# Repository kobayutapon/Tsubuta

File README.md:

# Tsubuta
Tsubuta is IoT device produced by GDG Shinshu

## Presentation
* [Presentation Document](./Document/Tsubuta_Presentation.pdf.pdf)

## Hardware Information  
* [Hardware Specification](./Hardware/BoardSpec.md)
* [Board schematic](./Hardware/Tsubuta_Schematic.pdf)
* [Firmware](./Hardware/Arduino/Tsubuta_AddOnBoard/Tsubuta_AddOnBoard.ino)

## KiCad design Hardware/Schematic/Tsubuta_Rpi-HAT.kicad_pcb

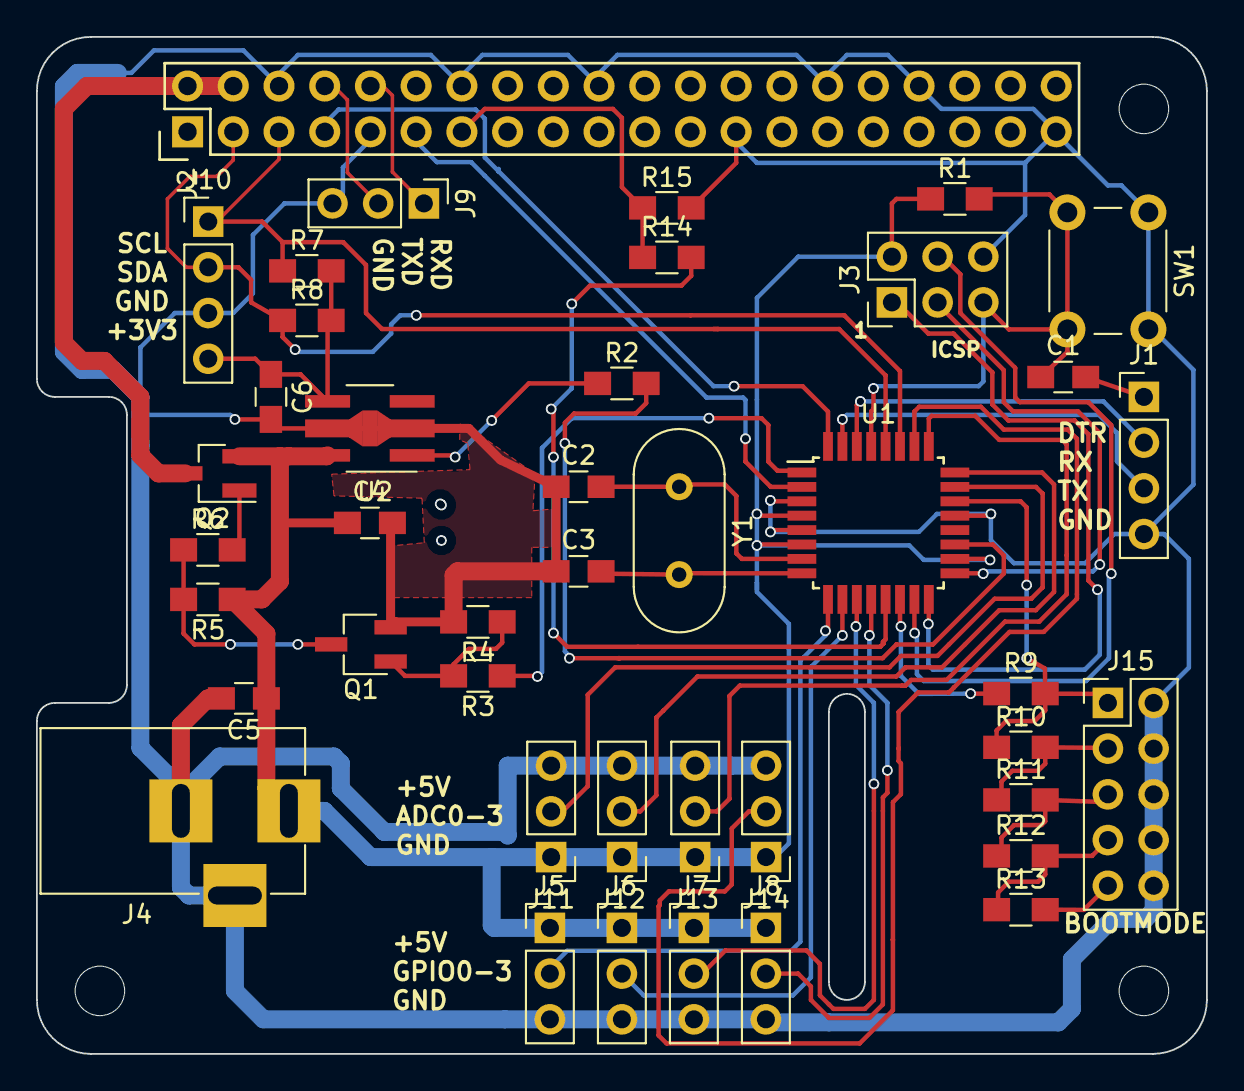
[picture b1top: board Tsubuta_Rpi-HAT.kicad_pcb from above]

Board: 2 copper layers, 65.0 x 56.5 mm, 42 parts (0 on the bottom side), 41 nets.

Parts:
C1: 0.1uF; C_0805_HandSoldering
C2, C3: 22pF; C_0805_HandSoldering
C4: 0.33uF; C_0805_HandSoldering
C5: 22uF; C_0805_HandSoldering
C6: 2.2uF; C_0805_HandSoldering
J1: Conn_01x04; Pin_Header_Straight_1x04_Pitch2.54mm
J2: RPi_GPIO; Pin_Header_Straight_2x20
J3: CN_ICSP; Pin_Header_Straight_2x03_Pitch2.54mm
J4: Jack-DC; BARREL_JACK
J5: GPIO0; Pin_Header_Straight_1x03_Pitch2.54mm
J6: GPIO1; Pin_Header_Straight_1x03_Pitch2.54mm
J7: GPIO2; Pin_Header_Straight_1x03_Pitch2.54mm
J8: GPIO3; Pin_Header_Straight_1x03_Pitch2.54mm
J9: Conn_01x03; Pin_Header_Straight_1x03_Pitch2.54mm
J10: CN_I2C; Pin_Header_Straight_1x04_Pitch2.54mm
J11: ADC0; Pin_Header_Straight_1x03_Pitch2.54mm
J12: ADC1; Pin_Header_Straight_1x03_Pitch2.54mm
J13: ADC2; Pin_Header_Straight_1x03_Pitch2.54mm
J14: ADC3; Pin_Header_Straight_1x03_Pitch2.54mm
J15: BOOTMODE; Pin_Header_Straight_2x05_Pitch2.54mm
Q1: 2SC3325-Y; SC-59_Handsoldering
Q2: IRLML6402(SOT-23); SOT-23_Handsoldering
R1, R2, R3, R4, R5, R6, R7, R8, R9, R11, R12, R13: 10K; R_0805_HandSoldering
R10: 1K; R_0805_HandSoldering
R14: 1.8K; R_0805_HandSoldering
R15: 3.3K; R_0805_HandSoldering
SW1: SW_RST; SW_PUSH_6mm
U1: ATMEGA328P-AU; TQFP-32_7x7mm_Pitch0.8mm
U2: NJM2884U1; SOT-89-5_Housing_Handsoldering
Y1: 16MHz; Crystal_HC49-U_Vertical

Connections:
3V3_ENB: R2.2, U1.19
#ARD_SS: R9.1, U1.14
#RST: C1.1, J3.5, R1.2, SW1.2, U1.29
+3V3: C6.1, J10.4, R7.2, R8.2, U2.4
+5V: C4.1, C5.1, J3.2, J4.1, J5.1, J6.1, J7.1, J8.1, J11.1, J12.1, J13.1, J14.1, Q2.2, R1.1, R5.1, U1.4, U1.6, U1.18, U2.5
ADC0: J11.2, U1.23
ADC1: J12.2, U1.24
ADC2: J13.2, U1.25
ADC3: J14.2, U1.26
ARD_INT_3V3: J2.13, R14.1, R15.1
ARD_INT_5V: R14.2, U1.13
ARD_MISO: J3.1, U1.16
ARD_MOSI: J3.4, U1.15
ARD_RX: J1.2, U1.30
ARD_SCK: J3.3, U1.17
ARD_SCL: J2.5, J10.1, R7.1, U1.28
ARD_SDA: J2.3, J10.2, R8.1, U1.27
ARD_TX: J1.3, U1.31
ARD_XTAL1: C2.2, U1.7, Y1.1
ARD_XTAL2: C3.2, U1.8, Y1.2
BOOTMODE: J15.1, R9.2, R10.1, U1.22
GND: C2.1, C3.1, C4.2, C5.2, C6.2, J1.4, J2.6, J2.9, J2.14, J2.20, J2.25, J2.30, J2.34, J2.39, J3.6, J4.2, J4.3, J5.3, J6.3, J7.3, J8.3, J9.3, J10.3, J11.3, J12.3, J13.3, J14.3, J15.2, J15.4, J15.6, J15.8, J15.10, Q1.2, R4.2, R15.2, SW1.1, U1.3, U1.5, U1.21, U2.2
GPIO0: J5.2, U1.9
GPIO1: J6.2, U1.10
GPIO2: J7.2, U1.11
GPIO3: J8.2, U1.12
unnamed: C1.2, J1.1
unnamed: J15.3, R10.2, R11.1
unnamed: J15.5, R11.2, R12.1
unnamed: J15.7, R12.2, R13.1
unnamed: J15.9, R13.2
unnamed: Q1.1, R3.2, R4.1
unnamed: Q1.3, R5.2, R6.1
unnamed: Q2.1, R6.2
unnamed: R2.1, U2.1
PWR_OFF: J2.11, U1.2
RPI_5V: J2.2, J2.4, Q2.3
RPI_INT: J2.7, U1.32
RPI_RXD: J2.10, J9.1
RPI_TXD: J2.8, J9.2
RPPWR: R3.1, U1.1

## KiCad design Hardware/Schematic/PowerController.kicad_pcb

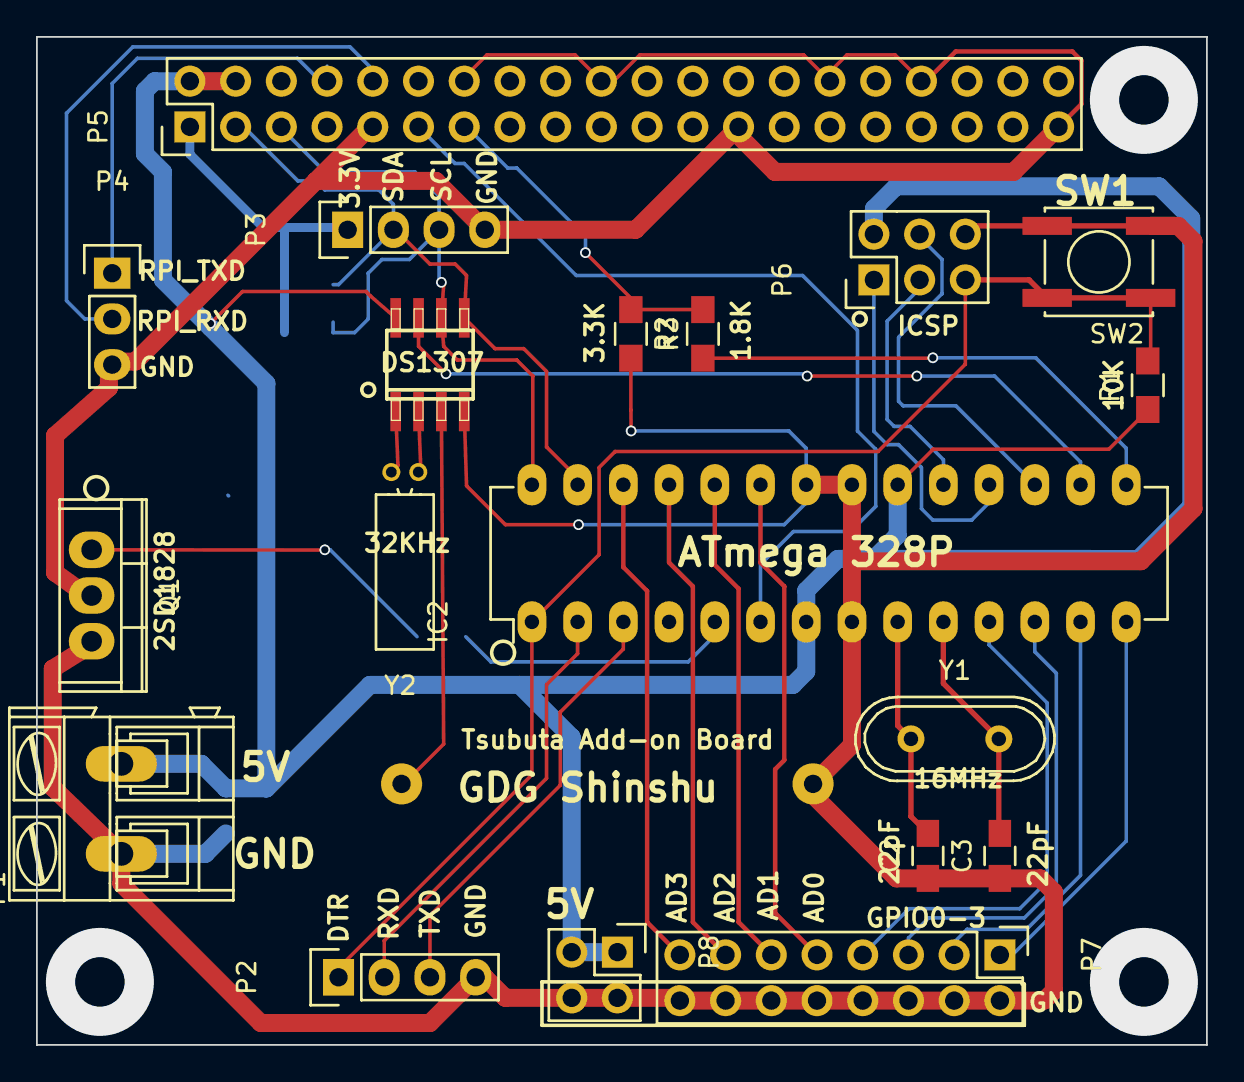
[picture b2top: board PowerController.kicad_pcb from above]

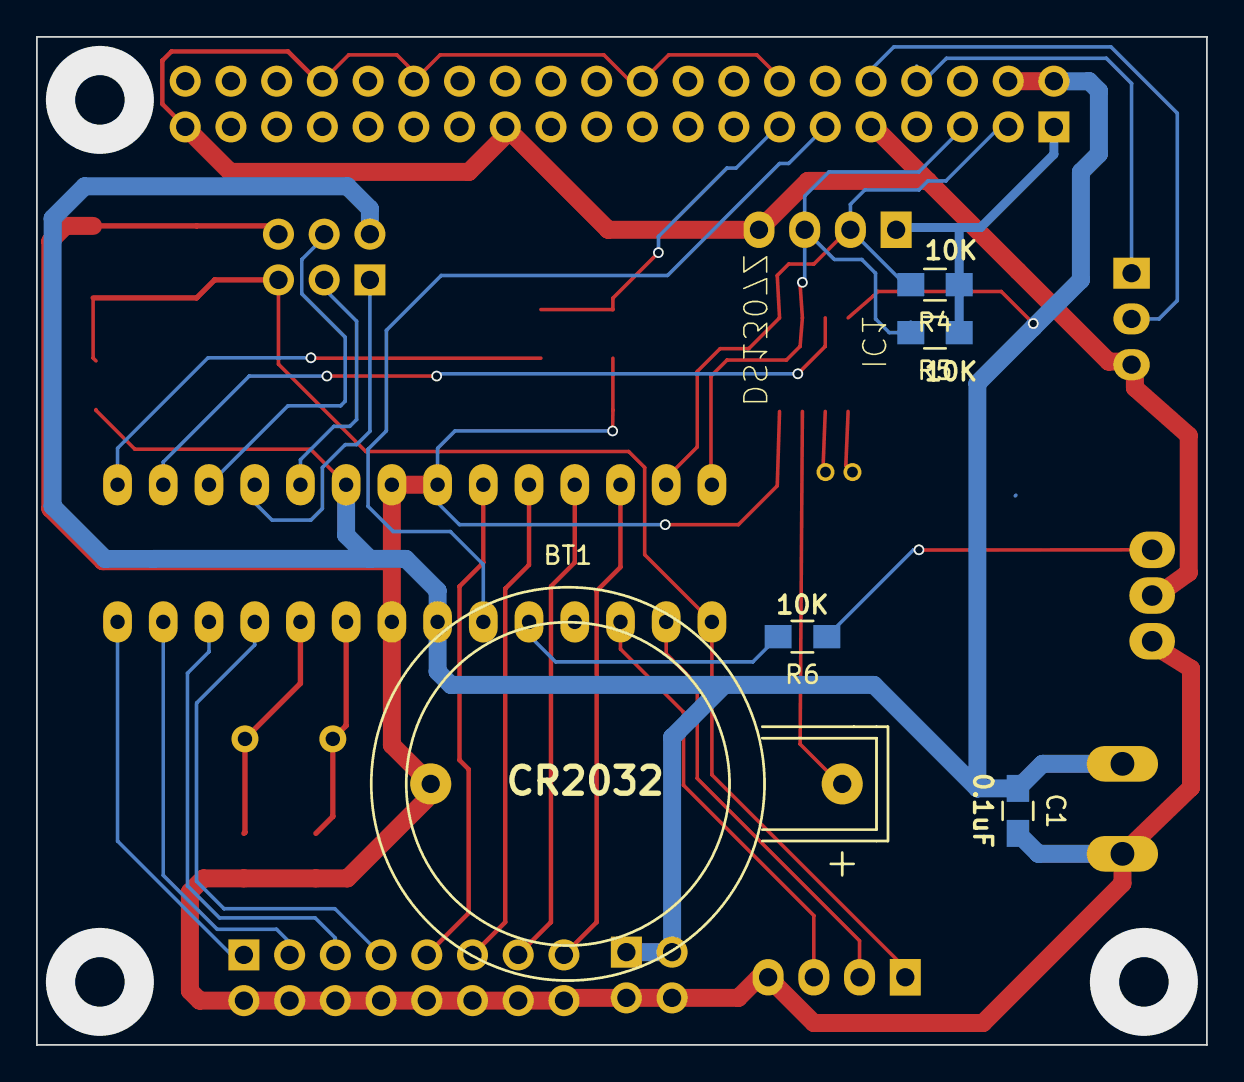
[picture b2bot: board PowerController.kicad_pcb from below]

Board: 2 copper layers, 65.0 x 56.0 mm, 24 parts (5 on the bottom side), 33 nets.

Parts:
BT1: CR2303; CR2032H
C1: 22u; C_0805_HandSoldering
C2, C3: 22p; C_0805_HandSoldering
IC1: DS1307Z; ds1307_pcf8583-SOIC8
IC2: ATMEGA328-P; DIP-28_W7.62mm_LongPads
P1: CONN_POWER; AK300-2
P2: CONN_AVR_UART; Pin_Header_Straight_1x04
P3: CONN_I2C; Pin_Header_Straight_1x04
P4: CONN_UART; Pin_Header_Straight_1x03
P5: CONN_02X20; Pin_Header_Straight_2x20
P6: ICSP; Pin_Header_Straight_2x03
P7: CONN_02X08; Pin_Header_Straight_2x08
P8: CONN_02X02; Pin_Header_Straight_2x02
Q1: Q_NPN_BCE; TO-220
R1, R4, R5, R6: 10K; R_0805_HandSoldering
R2: 1.8K; R_0805_HandSoldering
R3: 3.3K; R_0805_HandSoldering
SW2: SW_PUSH; SW_SPST_EVPBF
Y1: 16MHz; Crystal_HC49-U_Vertical
Y2: 32KHz; Crystal_Round_Horizontal_3mm

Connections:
+5V: C1.1, IC1.8, IC2.7, IC2.20, P1.2, P5.2, P5.4, P6.2, P8.1, P8.3, R1.1
/AD0: IC2.23, P7.9
/AD1: IC2.24, P7.11
/AD2: IC2.25, P7.13
/AD3: IC2.26, P7.15
/A_SCL: IC1.6, IC2.28, P3.3, P5.5, R5.2
/A_SDA: IC1.5, IC2.27, P3.2, P5.3, R4.2
/A_SQW: IC1.7, IC2.16
/GPIO0: IC2.11, P7.7
/GPIO1: IC2.12, P7.5
/GPIO2: IC2.13, P7.3
/GPIO3: IC2.14, P7.1
/PWR_OFF: IC2.6, P5.11
/RPPWR: IC2.5, R6.2
/RPPWR_GND: P3.4, P4.3, P5.9, P5.14, P5.20, P5.25, P5.30, P5.34, P5.39, Q1.2
/RST: IC2.1, P2.1, P6.5, R1.2, SW2.1
GND: BT1.2, C1.2, C2.1, C3.1, IC1.4, IC2.8, IC2.21, IC2.22, P1.1, P2.4, P6.6, P7.2, P7.4, P7.6, P7.8, P7.10, P7.12, P7.14, P7.16, P8.2, P8.4, Q1.3, R3.2, SW2.2
unnamed: BT1.1, IC1.3
unnamed: C2.2, IC2.9, Y1.1
unnamed: C3.2, IC2.10, Y1.2
unnamed: IC1.1, Y2.2
unnamed: IC1.2, Y2.1
unnamed: IC2.2, P2.2
unnamed: IC2.3, P2.3
unnamed: IC2.15, R2.1
unnamed: IC2.17, P6.4
unnamed: IC2.18, P6.1
unnamed: IC2.19, P6.3
unnamed: P3.1, P5.1, R4.1, R5.1
unnamed: P4.1, P5.8
unnamed: P4.2, P5.10
unnamed: P5.13, R2.2, R3.1
unnamed: Q1.1, R6.1

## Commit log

2016-03-27 新規作成 ・Tsubuta Rev.2向け 回路図/ガーバーデータ Arduino用ソフトウエア
2016-03-27 PDF版の回路図を追加
2016-05-13 I2Cコマンド受信処理を修正
2016-05-14 I2Cコマンドを追加・修正
2016-05-14 Modify readme
2016-05-14 プレゼンテーション資料を追加
2016-05-14 ファイル削除
2016-05-14 プレゼン資料追加
2016-06-06 Add Script files
2018-01-20 3Dプリンタ用のメカデータ追加(FreeCAD用データ)
2018-01-20 Tsubuta Rev2 ボード Rpi-HAT外形に準拠 RTC削除
2018-01-20 アノテーション修正
2018-01-20 内部処理を見直し 電源シーケンス見直し バッテリー残量警告追加
2018-01-20 バッテリー残量閾値を見直し
